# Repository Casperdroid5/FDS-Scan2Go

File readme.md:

# FDS-Scan2Go

## Overview
The Ferrous Metal Detection Gate (FDS) is a sophisticated system designed to enhance safety for MRI room access by detecting ferrous metals. This system utilizes a Raspberry Pi Pico and Raspberry Pi 5 to facilitate communication with various sensors, providing both auditory and visual feedback to the user.

## Table of Contents
- [Features](#features)
- [Hardware Requirements](#hardware-requirements)
- [Software Setup](#software-setup)
- [Installation](#installation)
  - [Raspberry Pi Pico](#raspberry-pi-pico)
  - [Raspberry Pi 5](#raspberry-pi-5)
- [Usage](#usage)
- [Contributing](#contributing)
- [License](#license)

## Features
- Utilizes a ferrous metal detector for metal detection
- Provides auditory and visual feedback to the user
- Employs both Raspberry Pi Pico and Raspberry Pi 5
- Communicates with multiple sensors for enhanced detection accuracy

## Hardware Requirements
### Raspberry Pi Pico
- All the wanted peripherals (buttons, sensors etc.)
- Micro usb cable (ensure it has data wires)

### Raspberry Pi 5
- Raspberry Pi 25W, power supply
- USB to 3.5mm audio adapter
- Display/monitor for imageoutput
- MicroHDMI to HDMI adapter 

## Software Setup
### Prerequisites
- Python 3.12 or higher
- Required Python libraries (listed in `requirements_rpi5.txt` for Raspberry Pi 5)
- MicroPython libraries for Raspberry Pi Pico (listed in `requirements_pico.txt`)

## Installation
### Raspberry Pi Pico

1. **Install Dependencies**
   Since the Pico runs on MicroPython for this project, you'll need to upload the required libraries manually or use a tool like `mpremote`.

   ```sh
   mpremote mip install micropython-neopixel micropython-machine micropython-time micropython-i2c micropython-uart
   ```

2. **Upload Scripts to Pico**
   Upload the relevant `.py` files to the Pico:
   ```sh
   mpremote fs cp hardware_s2g.py :hardware_s2g.py
   mpremote fs cp system_utils.py :system_utils.py
   mpremote fs cp main.py :main.py
   ```

### Raspberry Pi 5
1. **Prepare MicroSD Card**
   Install Raspbian 64-bit (with desktop) on a 32GB MicroSD card (using Raspberry Pi Imager, for example). Once installed, boot the Raspberry Pi 5, connect it to the internet, and open a terminal with root permissions.

2. **Install Python Dependencies**
   ```sh
   pip install -r requirements_rpi5.txt
   ```

3. **Install System Dependencies**
   ```sh
   sudo apt-get update
   sudo apt-get install feh vlc
   ```

4. **Run the Application**
   Navigate to the project directory and start the main script:
   ```sh
   python main.py
   ```

## Usage
1. **Connect the Raspberry Pi Pico and Raspberry Pi 5 via a MicroUSB cable.**
2. **Start the `main.py` script on the Raspberry Pi 5.**
3. The system will initialize, and the sensors will begin to monitor for ferrous metals. The NeoPixel LEDs and the display will provide feedback based on the detection status.

## Contributing
We welcome contributions to the FDS-Scan2Go project. If you would like to contribute, please fork the repository and submit a pull request. 

If you would like to emplement this code into your own project, ensure to give credit to the original author and mention any significant changes or improvements.

## Disclaimer
This project is licensed under the MIT License. See the [DISCLAIMER](/Software/DISCLAIMER.md) file for more details.

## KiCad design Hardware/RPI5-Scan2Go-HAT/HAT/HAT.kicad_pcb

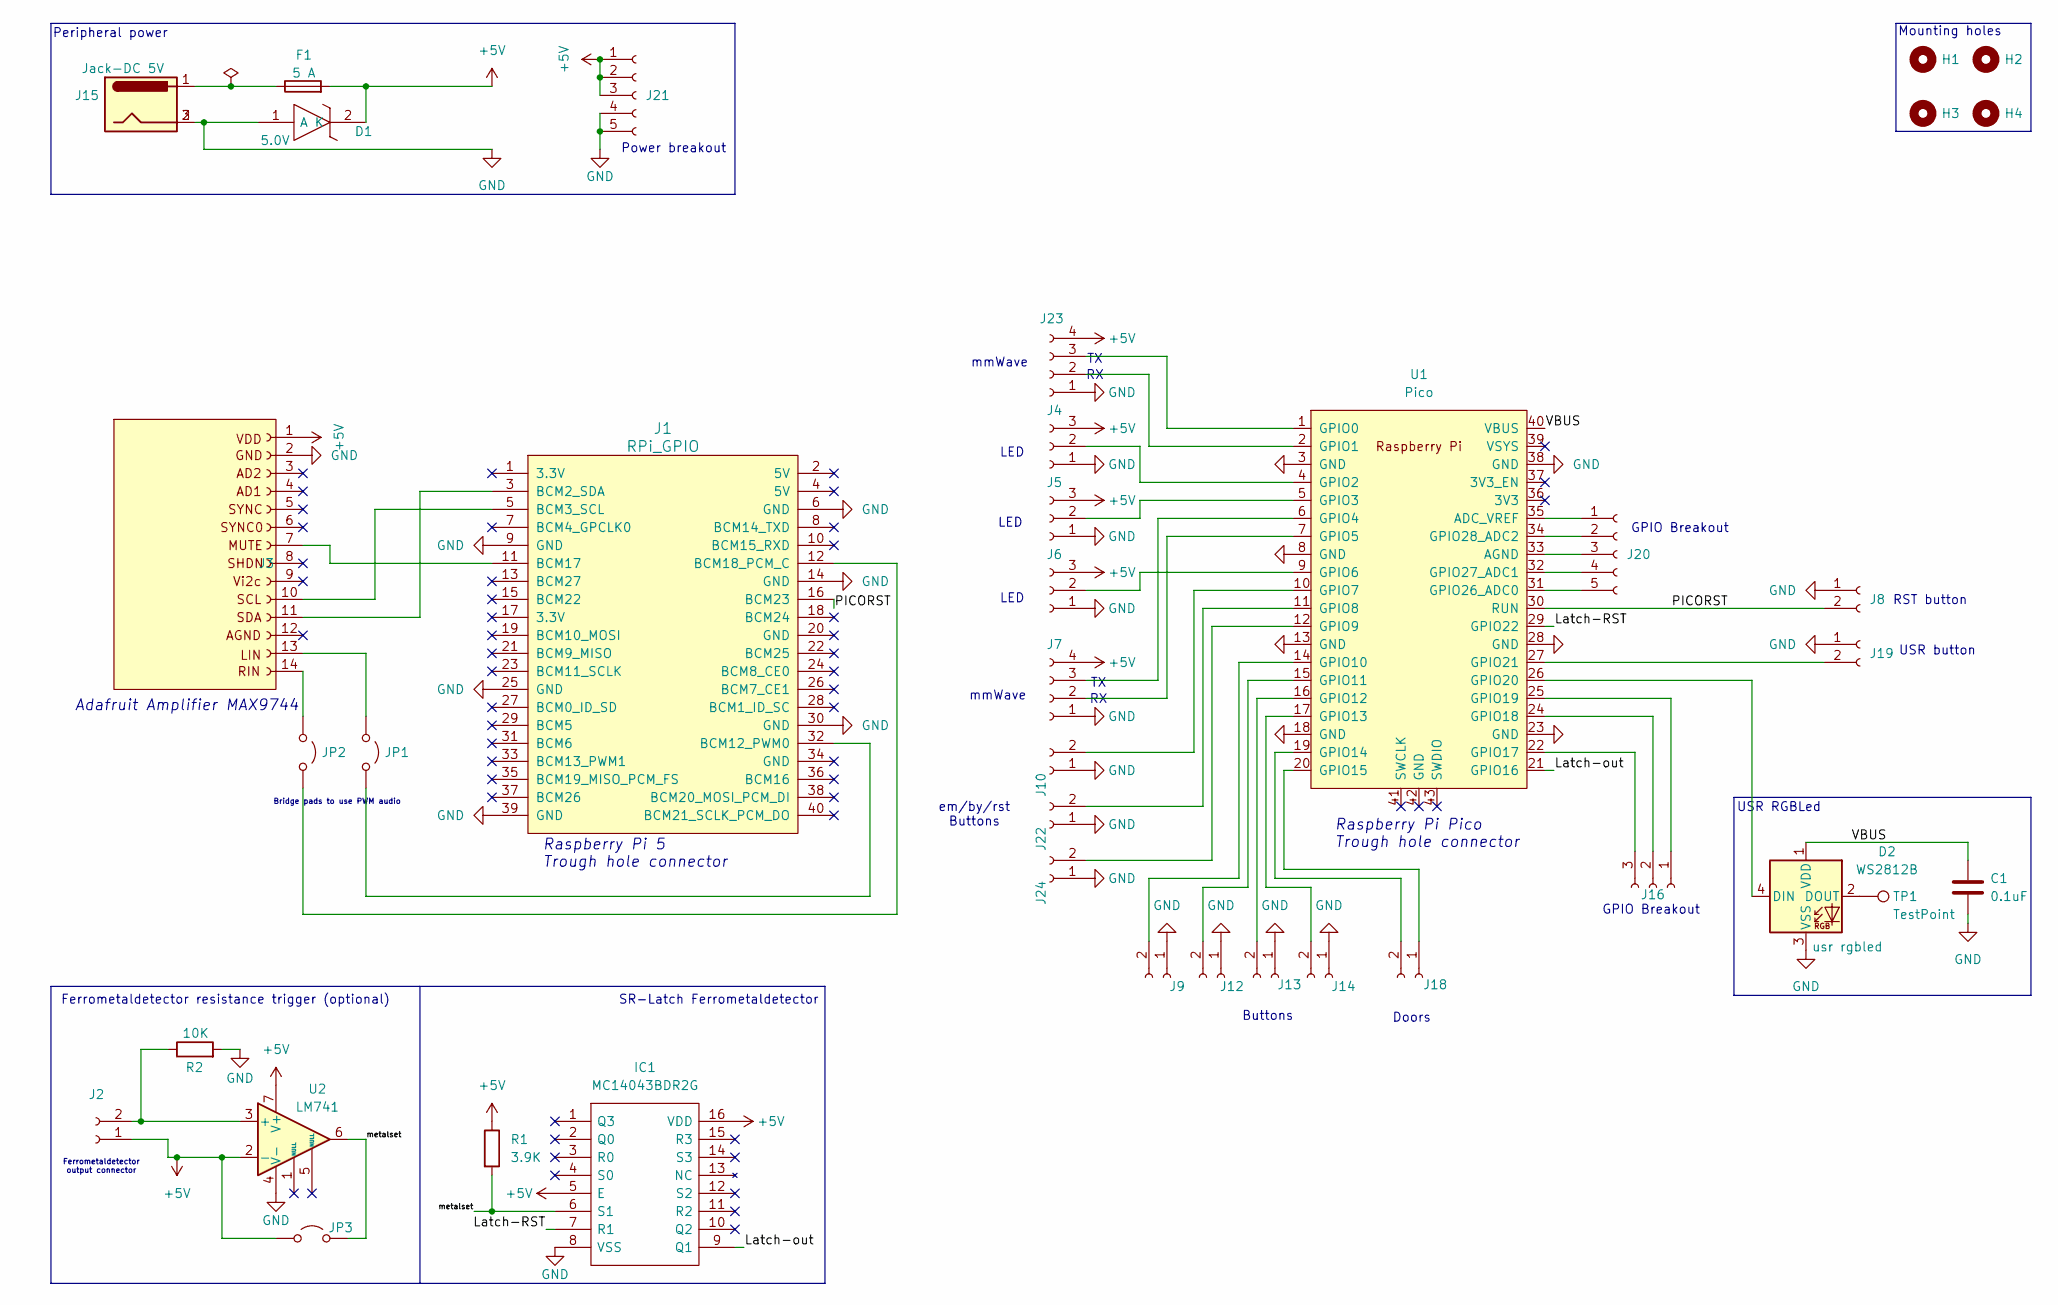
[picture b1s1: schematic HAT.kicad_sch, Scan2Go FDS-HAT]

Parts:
C1: 0.1uF; C_1206_3216Metric_Pad1.33x1.80mm_HandSolder; Mouser 581-12066D104KAT4A
D1: 5.0V; DIOM5436X261N; LCSC C10216
D2: WS2812B; LED_WS2812B_PLCC4_5.0x5.0mm_P3.2mm; Mouser 474-COM-16346
F1: 5 A; Fuse_2010_5025Metric_Pad1.52x2.65mm_HandSolder; LCSC C136353
H1, H2, H3, H4: MountingHole; MountingHole_3.2mm_M3
IC1: MC14043BDR2G; SOIC127P600X175-16N; Mouser Part Number 863-MC14043BDR2G
J1: RPi_GPIO; Pin_Header_Straight_2x20; Mouser 474-PRT-14017
J2, J8, J9, J10, J12, J13, J14, J18, J19, J22, J24: Conn_01x02_Socket; JST_EH_B2B-EH-A_1x02_P2.50mm_Vertical; Farnell 2399159
J3: Conn_01x14_Socket; PinSocket_1x14_P2.54mm_Vertical
J4, J5, J6, J16: Conn_01x03_Socket; JST_EH_B3B-EH-A_1x03_P2.50mm_Vertical; Farnell 2399161
J7, J23: Conn_01x04_Socket; JST_EH_B4B-EH-A_1x04_P2.50mm_Vertical; Farnell 1830714
J15: Jack-DC 5V; BarrelJack_Wuerth_6941xx301002; Farnell FCR681466P
J20, J21: Conn_01x05_Socket; JST_EH_B5B-EH-A_1x05_P2.50mm_Vertical; Farnell 1830716
JP1, JP2, JP3: Jumper_2_Open; SolderJumper-2_P1.3mm_Open_TrianglePad1.0x1.5mm
R1: 3.9K; R_1206_3216Metric_Pad1.30x1.75mm_HandSolder; Farnell 3545485
R2: 10K; R_1206_3216Metric_Pad1.30x1.75mm_HandSolder; Farnell 3545485
TP1: TestPoint; TestPoint_Pad_2.0x2.0mm
U1: Pico; RPi_Pico_SMD_TH; Mouser 358-SC0915
U2: LM741; SOIC-8_3.9x4.9mm_P1.27mm; Farnell 3117118

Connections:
+5V: D1.2 (K), F1.2, IC1.5 (E), IC1.16 (VDD), J2.1, J3.1 (VDD), J4.3, J5.3, J6.3, J7.4, J21.1, J21.2, J21.3, J23.4, JP3.1 (A), R1.1, U2.2 (-), U2.7 (V+)
/Latch-RST: IC1.7 (R1), U1.29 (GPIO22)
/Latch-out: IC1.9 (Q1), U1.21 (GPIO16)
/PICORST: J1.16 (BCM23), J8.2, U1.30 (RUN)
/VBUS: C1.1, D2.1 (VDD), U1.40 (VBUS)
/metalset: IC1.6 (S1), JP3.2 (B), R1.2, U2.6
GND: C1.2, D1.1 (A), D2.3 (VSS), IC1.8 (VSS), J1.6 (GND), J1.9 (GND), J1.14 (GND), J1.25 (GND), J1.30 (GND), J1.39 (GND), J3.2 (GND), J4.1, J5.1, J6.1, J7.1, J8.1, J9.1, J10.1, J12.1, J13.1, J14.1, J15.2, J15.3, J19.1, J21.4, J21.5, J22.1, J23.1, J24.1, R2.2, U1.3 (GND), U1.8 (GND), U1.13 (GND), U1.18 (GND), U1.23 (GND), U1.28 (GND), U1.38 (GND), U2.4 (V-)
unnamed: D2.4 (DIN), U1.26 (GPIO20)
unnamed: D2.2 (DOUT), TP1.1
unnamed: F1.1, J15.1
unnamed: J1.3 (BCM2_SDA), J3.11 (SDA)
unnamed: J1.5 (BCM3_SCL), J3.10 (SCL)
unnamed: J1.32 (BCM12_PWM0), JP1.2 (B)
unnamed: J1.11 (BCM17), J3.7 (MUTE)
unnamed: J1.12 (BCM18_PCM_C), JP2.2 (B)
unnamed: J2.2, R2.1, U2.3 (+)
unnamed: J3.13 (LIN), JP1.1 (A)
unnamed: J3.14 (RIN), JP2.1 (A)
unnamed: J4.2, U1.4 (GPIO2)
unnamed: J5.2, U1.5 (GPIO3)
unnamed: J6.2, U1.9 (GPIO6)
unnamed: J7.2, U1.7 (GPIO5)
unnamed: J7.3, U1.6 (GPIO4)
unnamed: J9.2, U1.14 (GPIO10)
unnamed: J10.2, U1.10 (GPIO7)
unnamed: J12.2, U1.15 (GPIO11)
unnamed: J13.2, U1.16 (GPIO12)
unnamed: J14.2, U1.17 (GPIO13)
unnamed: J16.1, U1.25 (GPIO19)
unnamed: J16.2, U1.24 (GPIO18)
unnamed: J16.3, U1.22 (GPIO17)
unnamed: J18.1, U1.20 (GPIO15)
unnamed: J18.2, U1.19 (GPIO14)
unnamed: J19.2, U1.27 (GPIO21)
unnamed: J20.1, U1.35 (ADC_VREF)
unnamed: J20.2, U1.34 (GPIO28_ADC2)
unnamed: J20.3, U1.33 (AGND)
unnamed: J20.4, U1.32 (GPIO27_ADC1)
unnamed: J20.5, U1.31 (GPIO26_ADC0)
unnamed: J22.2, U1.11 (GPIO8)
unnamed: J23.2, U1.2 (GPIO1)
unnamed: J23.3, U1.1 (GPIO0)
unnamed: J24.2, U1.12 (GPIO9)

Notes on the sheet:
mmWave
Adafruit Amplifier MAX9744
LED
Bridge pads to use PWM audio
USR button
Buttons
GPIO Breakout
RST button
Doors
Raspberry Pi Pico Trough hole connector
Mounting holes
Ferrometaldetector resistance trigger (optional)
USR RGBLed
Peripheral power
Raspberry Pi 5 Trough hole connector
em/by/rst Buttons
SR-Latch Ferrometaldetector
Ferrometaldetector output connector
Power breakout

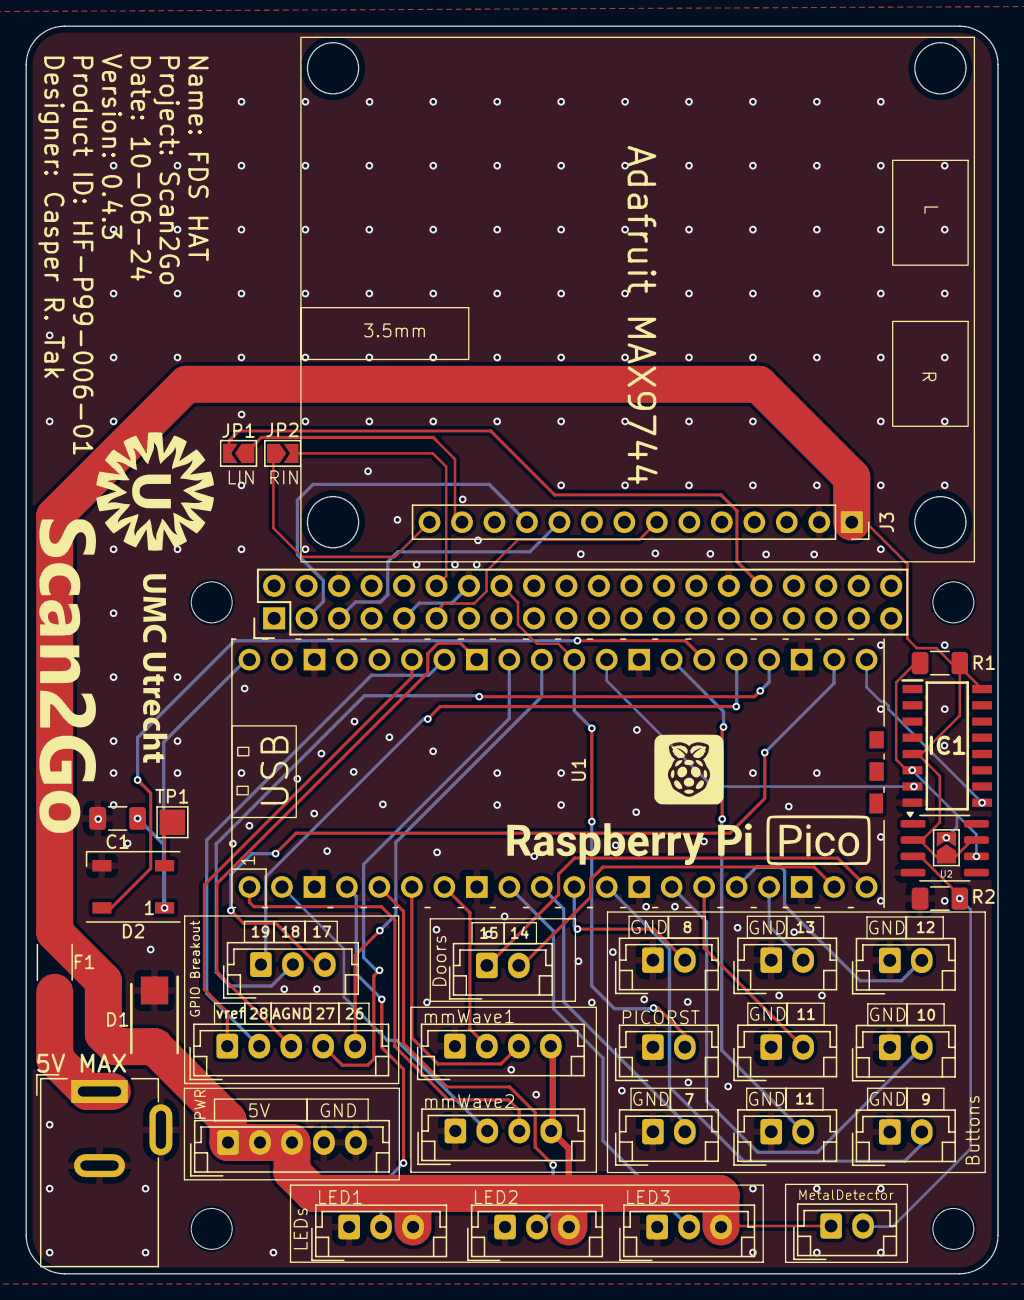
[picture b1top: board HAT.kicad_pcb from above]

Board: 2 copper layers, 76.0 x 97.6 mm, 39 parts (0 on the bottom side), 43 nets.

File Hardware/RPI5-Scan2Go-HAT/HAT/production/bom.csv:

Designator,Footprint,Quantity,Value,LCSC Part #
C1,1206,1,0.1uF,
D1,DIOM5436X261N,1,5.0V,C10216
D2,LED_WS2812B_PLCC4_5.0x5.0mm_P3.2mm,1,WS2812B,
F1,2010,1,5 A,C136353
IC1,SOIC127P600X175-16N,1,MC14043BDR2G,
J1,Pin_Header_Straight_2x20,1,RPi_GPIO,
"J10, J11, J12, J13, J14, J18, J19, J22, J24, J8, J9",JST_EH_B2B-EH-A_1x02_P2.50mm_Vertical,11,Conn_01x02_Socket,
J15,BarrelJack_Wuerth_6941xx301002,1,Jack-DC 5V,
"J16, J4, J5, J6",JST_EH_B3B-EH-A_1x03_P2.50mm_Vertical,4,Conn_01x03_Socket,
"J20, J21",JST_EH_B5B-EH-A_1x05_P2.50mm_Vertical,2,Conn_01x05_Socket,
"J23, J7",JST_EH_B4B-EH-A_1x04_P2.50mm_Vertical,2,Conn_01x04_Socket,
J3,PinSocket_1x14_P2.54mm_Vertical,1,Conn_01x14_Socket,
"JP1, JP2",SolderJumper-2_P1.3mm_Open_TrianglePad1.0x1.5mm,2,Jumper_2_Open,
TP1,TestPoint_Pad_2.0x2.0mm,1,TestPoint,
U1,RPi_Pico_SMD_TH,1,Pico,

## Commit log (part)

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2024-02-23 First Pico program: blink init
2024-02-26 RGBLED testcode finished
2024-02-26 wrote unittest (not function yet
2024-02-26 oled driver 1306
2024-02-26 i2c oled driver added
2024-02-26 added folders (cleanup)
2024-02-26 removed testcode from button.py
2024-02-26 reverted issue
2024-02-27 Created potmeter class and test
2024-02-27 first objects made in main
2024-02-27 created led and led test
2024-02-27 renamed LED class to pwm
2024-02-27 finished creating objects and pin assignment
2024-02-28 simple state machine udelizing buttons and oled.
2024-02-28 ingevulde statemachine, oled werkt, schakelaars werken, states zijn rommelig
2024-02-28 ferro detection potmeter with rgb state functional
2024-02-28 improved state
2024-02-29 changed statemachine states in text-form
2024-02-29 added servo code and test code
2024-02-29 removed stupid lambda fucntion.
2024-02-29 created state machine with terminal choice input
2024-03-01 Niveau 1 complete of state machine.
2024-03-04 Niveau 2 complete of state machine
2024-03-05 Niveau 3 complete
2024-03-05 improved Niveau 3, broke scan LED
2024-03-05 Finished Niveau 4 (now with scanled)
2024-03-05 minor code improvements
2024-03-06 Finished Niveau 5 (emergency button)
2024-03-06 Brightness lowerd of oled and cleanup
2024-03-07 minor changes and added nuke file
2024-03-07 freeze bug fix
2024-03-08 removed overhead classes
2024-03-08 removed overhead code from main
2024-03-11 first version of empty new state machine
2024-03-11 state machine filled in, first approach
2024-03-11 First statemachine functionality empty machine, but running on RPI Pico
2024-03-11 first code revision. Non functional
2024-03-11 created hardware class
2024-03-11 replaced classes with hardware class atributes
2024-03-12 Killed the Oled off
2024-03-12 replaced oled with print
2024-03-12 statemachine seems to function (LEDS work)
2024-03-12 classes improved
2024-03-13 functional but adding more functions
2024-03-13 creating more classes (functions)
2024-03-13 chainged file names. added led and door motor
2024-03-14 periodic fix
2024-03-14 removed inherritance from hardwares2g.py
2024-03-14 mmWave sensor UART readout succesfull
2024-03-14 fixed github push error
2024-03-15 door unlock and lock functions
2024-03-18 added second uart input device, improved rgb led test
2024-03-18 improved error handling, showing output on screen
2024-03-18 improved minor details on error logging
2024-03-19 2 arguments given,1 expected. problem solved
2024-03-19 button implemented as function, but not functional because of timing probably
2024-03-19 renamed main to uasyncmain
2024-03-19 statemachine emergency button works (stops program)
2024-03-19 cleanup
2024-03-19 restored main.
2024-03-20 seperated emergency buttons
2024-03-20 improved naming conventions
2024-03-20 statemachine progress
2024-03-20 statemachine progress (better functioning metal detection handling states)
2024-03-20 cleanup (comments)
2024-03-20 more cleanuip
2024-03-20 changed user_field_A and B states logic
2024-03-20 added button logic (untested)
2024-03-21 added debounce to buttons
2024-03-21 field detector buttons added, next to door buttons (TBT = to be tested)
2024-03-21 working on scan_for_ferrometals (renamed scanner) and state transistions
2024-03-21 scan_for_ferrometals and buttons implemented, statemachine not finished
2024-03-21 metal detection state will be determined after person movement from field a to b (TBT)
2024-03-22 state machine basic functionality working (no stress testing yet)
2024-03-22 fixed the system_utils and main link
2024-03-22 Fixed the systems link for reall now
2024-03-22 fixed door 1 bug
2024-03-22 no idea
2024-03-22 renamed functions (field)
2024-03-22 merged person detectors into 1 function
2024-03-25 statemachine functional, (TBT) but irs not safe
2024-03-25 version to be tested
2024-03-25 improved state machine safety (returning from MRI)
2024-03-25 cleanup of unused variables and improved override buttons
2024-03-25 added system reset after emergency button pressed
2024-03-25 moved door functions
2024-03-25 door 2 can open when required.
2024-03-26 changed door function names (new function tbt)
2024-03-26 improved code (classes) now functional
2024-03-26 fixed declaration error
2024-03-26 corrected error in imports
2024-03-26 replaced person_detected_in_field logic with uart logic (non functional)
2024-03-26 trying to fix uart
2024-03-26 mmWave sensors implemented
2024-03-27 code seems to work with person detector
2024-03-27 trying new door sensors class
2024-03-27 improved door class by adding state linked to the handle_door1/2 functions in main. TBT
2024-03-27 improved declarations/inits of components in main
2024-03-27 removed buttons error in naming
2024-03-27 fixed the code
2024-03-28 replaced RGB LED with WS2812 in all files
2024-03-28 restored leds class
2024-03-28 user input via terminal to temporarly replace mmWave sensors (not stable)
2024-03-28 doors now showing state (open/closed) but emergency button and bypass failing to re-open
2024-03-29 improved state machine transistions
2024-03-29 minor improvements
2024-03-29 cleanup debugging
2024-04-02 writing logging function
2024-04-02 succesfull log function test
2024-04-02 buggy state machine
2024-04-02 Loggin seems to work again
2024-04-02 removed settting color from doorleds
2024-04-02 added final log messages
2024-04-02 rewriting state machine states (simpler = beter)
2024-04-02 ferrometal scanner interrupt added
2024-04-03 override fixed.
2024-04-04 Bug fixes on main after monkey tested it.
2024-04-05 send uart commands to rpi pico
2024-04-05 uartclass erbij gemaakt
2024-04-06 extended classes and messages
2024-04-06 removed log function from pico to txt file.
2024-04-08 fixed uart not communicating well bug
2024-04-08 rpi message reciever test
2024-04-08 working on communication both ways uart
2024-04-09 rewrote communication betweer RPI and PICO
2024-04-11 updated code for rpi and pico
2024-04-12 new mmWave sensor tested
2024-04-12 changed code to work with rpi pico led
2024-04-15 run_forever edited.
2024-04-15 functional person detector (TBT)
2024-04-15 test program fixed
2024-04-15 functional mmWave with doors
2024-04-15 trying to add debounce to mmWaves
2024-04-16 Better functioning state machine with mmWave.
2024-04-16 implemented debounce for people removed from scanner. (Timer to be implemented, now delay)
2024-04-16 barely functional debounce
2024-04-16 implemented non blocking timer for tests. TBT
2024-04-16 cleanup of old blocking timers
2024-04-16 Non blocking timer created
2024-04-16 minor improvements to timer
2024-04-16 functional FDS with mmWave
2024-04-16 Possibly fixed the door 1 slamming after finished procedure fds
2024-04-17 rewrote UARTcom for usb to rpi and pico setup
2024-04-17 moved class, renamed and altered mmwave classes and removed prints.
2024-04-17 minor improvements to formatting
2024-04-17 renamed class
2024-04-17 improved messaging
2024-04-18 implemented audio and image commands and added corresponding data files
2024-04-18 minor imrovements to image shower
2024-04-18 detached leds from doors and attached to mmWavesensors.
2024-04-18 images added... weird bug encountering Github
2024-04-18 minor changes to files
2024-04-18 moved audio and image controllers to system utils
2024-04-18 showing images for emergency and bypass
2024-04-18 added missing image line
2024-04-18 restored emergency button function
2024-04-18 init state improvements
2024-04-19 New sounds file names
2024-04-19 Sound handler improved
2024-04-19 fixed audio 9 not playing
2024-04-19 fixed audio bug, implenting new function to make it more encapsulated
2024-04-19 added extra image and reverted logic for image showing.
2024-04-19 FDS system seems to be functional for now
2024-04-19 trying to improve emergency and override states
2024-04-19 moved functions back
2024-04-19 bug where system won't exit state (bypass)
2024-04-19 trying old method for emergency states and such
2024-04-21 minor changes and mmWave class variables renamed
2024-04-21 Trying pulse code
2024-04-21 improvement made to emergency state and bypass
2024-04-21 freeze function expanded
2024-04-21 Reset button implemented, which resolves bug regarding emergency and bypass state
2024-04-21 Reset now actually resets full system, no matter what state it was in
2024-04-21 added loggin functionality back in.
2024-04-21 added extra loggin messages
2024-04-22 improved symbols of pico and rpi
2024-04-22 created footprint for Adafruit amplifier
2024-04-24 swapped mmWave sensors around, changed mmwave threshold
2024-04-26 added power circuit and improved documentation
2024-04-26 added footprints
2024-05-04 added doxygen compatible comments to main
2024-05-06 removed useless class
2024-05-06 added minor functionality to system utils and removed junk
2024-05-06 systemexit
2024-05-06 added file paths for audio and video in code
2024-05-06 added paths settings
2024-05-08 improved naming of variables
2024-05-08 added docstrings
2024-05-08 added docstrings to systemutils
2024-05-13 changed requirements and pcb format
2024-05-13 added 3d models to design
2024-05-13 started routing
2024-05-14 removed 5V from barel to pi and pico
2024-05-14 Silkscreen improvements and additions
2024-05-14 V0.2 Finished
    - added product ID
    - via stitching
    - improved silkscreen
2024-05-14 added fabrication files
2024-05-14 re-linked 3d models and exported 3d models
2024-05-14 added missing pico 3d model
2024-05-21 Updated PCB to v0.2.1, improved docs
2024-05-21 added V0.3 of pcb (srlatch) and added librarys
2024-05-21 rewrote FDS code to set an reset SR-latch and read ferrometal input
2024-05-22 improved documentation
2024-05-23 Big refactor of all the code following SOLID principles
2024-05-23 updated old source code
2024-05-23 fixed solid code?
2024-05-23 minor improvements to startup (log)
2024-05-23 changed pin # for bypass
2024-05-24 created non blocking pulsing test code
2024-05-24 functional pulsing, but needs tweaking of numbers
2024-05-24 Brightness now doens't effect pulse speed
2024-05-24 multithreading functional and 'gracefull' exit.
2024-05-24 working on multithreading functionality
2024-05-24 Pulsing works without blocking or crashing!!
2024-05-27 main.py upated minor changes to specifications
2024-05-27 removed al _thread code (it's not safe)
2024-05-28 latch implemented in software
2024-05-29 integration uasyncio for pusling leds
2024-05-29 pulsing works, but mmWave now not resposive at all
2024-05-29 added comments to images and audio
2024-05-29 extra comments for emergency and bypass
2024-05-29 updated test code mmwave
2024-05-29 code restored
2024-05-29 removed print statement floodign
2024-05-29 removed unessecary overhead code
2024-05-31 removed user input
2024-05-31 seems to function with user input
2024-05-31 restored to mmwave sensors functionality
2024-06-01 FDS functional (it seems)
2024-06-01 updated hardware class person detector seeed
2024-06-01 added standing timet to seeed (not working yet)
2024-06-01 now correctly
2024-06-03 fixed timer bug in hardware class (mmwave)
2024-06-03 Old code with new features for DEMO
2024-06-03 minor changes, opening fullscreen images and mmWave settings (timers)
2024-06-05 updated PCB design to 0.4
    - added amplifier trigger to schematic and pcb
2024-06-05 bom(s) updated. 3d models added.
2024-06-10 PCB updated to V0.4.1
    -improvements in holes for audio amplifier
2024-06-10 made opamp in design optional
2024-06-10 New RPI5 program handling absent PICO
2024-06-10 added Pico detection handler to RPI
2024-06-17 Fixed Capacitor schematic error
2024-06-17 added LEDboard to code
2024-06-17 error handling for rpi5 not connected
2024-06-17 Communication and startup check between RPI and PICO realised
2024-06-17 added send_message function to RPI, was missing...
2024-06-17 Communication between PI en PICO now realised.
2024-06-17 implemented system health checker (function only)
2024-06-17 RPI5 Health function massively improved. Less blocking.
2024-06-17 added healthcheck troughout statemachine states
2024-06-18 Cleanup and added readme.md
